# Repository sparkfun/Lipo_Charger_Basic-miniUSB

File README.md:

SparkFun Lipo Charger Basic - miniUSB
=======================================

[*SparkFun Lipo Charger Basic - miniUSB (PRT-10401)*](https://www.sparkfun.com/products/10401)

If you need to charge LiPo batteries, this simple charger will do just that. It is designed to charge single-cell Li-Ion or Li-Polymer batteries.
The board incorporates a charging circuit, status LED, connector for your battery (JST-type used in the batteries we carry), and a mini-USB connector.

Repository Contents
-------------------
* **/Hardware** - All Eagle design files (.brd, .sch)

License Information
-------------------
The hardware is released under [Creative Commons ShareAlike 4.0 International](https://creativecommons.org/licenses/by-sa/4.0/).

Distributed as-is; no warranty is given.

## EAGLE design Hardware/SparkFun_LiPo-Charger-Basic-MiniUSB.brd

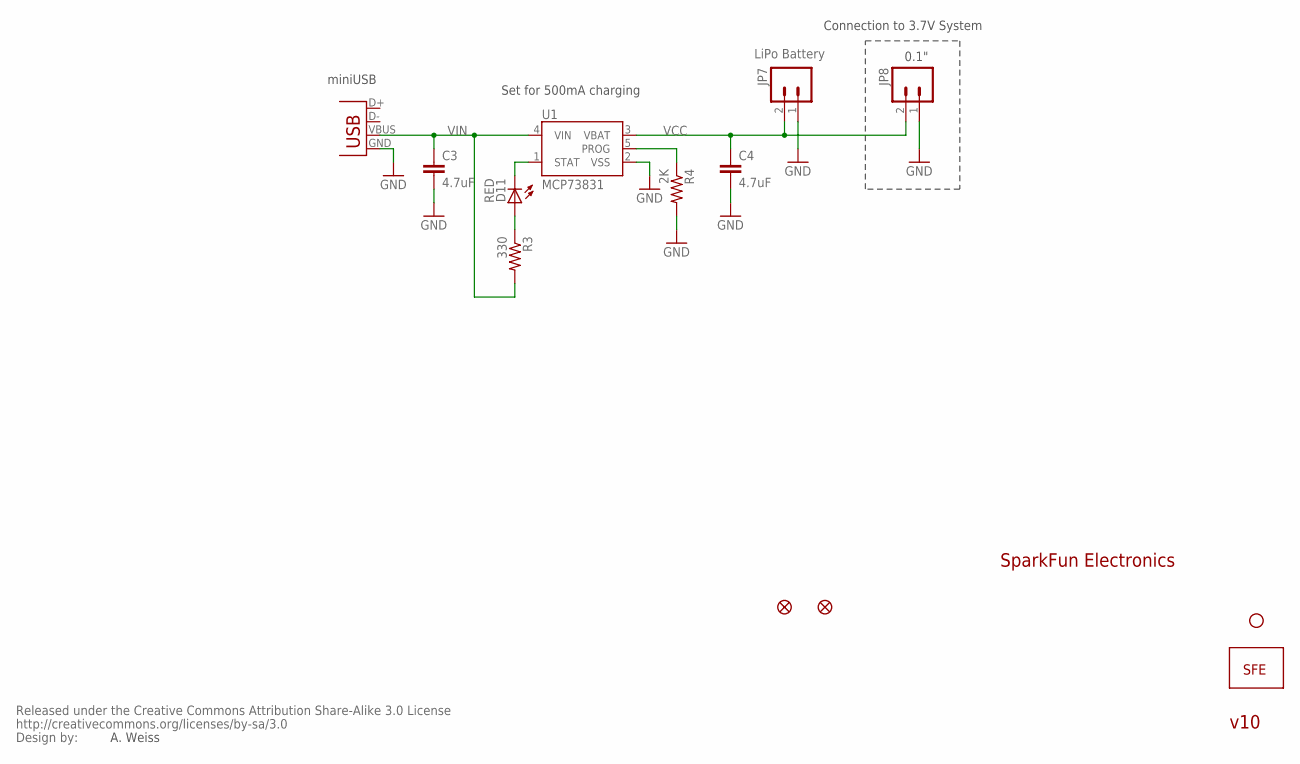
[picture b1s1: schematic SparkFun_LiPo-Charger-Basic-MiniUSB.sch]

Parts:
C3, C4: 4.7uF; 0402-CAP
D11: RED; LED-0603
JP1: LOGO-SFESK; SFE-LOGO-FLAME
JP2: STAND-OFF
JP3, JP4: FIDUCIAL1X2; FIDUCIAL-1X2
JP7: LiPo Battery; JST-2-SMD
JP8: M02PTH; 1X02
R3: 330; 0402-RES
R4: 2K; 0402-RES
U1: MCP73831; SOT23-5
U$1: CREATIVE_COMMONS
X1: Micro USB; USB-MINIB

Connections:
GND: C3.2, C4.2, JP7.1, JP8.1, R4.2, U1.2 (VSS), X1.GND
unnamed: D11.A, R3.1
PROG: R4.1, U1.5 (PROG)
STAT: D11.C, U1.1 (STAT)
VCC: C4.1, JP7.2, JP8.2, U1.3 (VBAT)
VIN: C3.1, R3.2, U1.4 (VIN), X1.VBUS

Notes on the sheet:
Set for 500mA charging
Connection to 3.7V System
0.1"
A. Weiss
miniUSB
v10
SparkFun Electronics

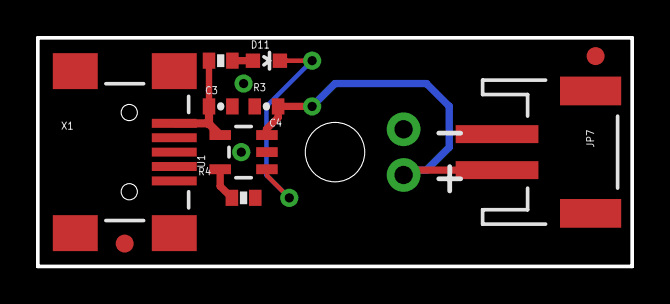
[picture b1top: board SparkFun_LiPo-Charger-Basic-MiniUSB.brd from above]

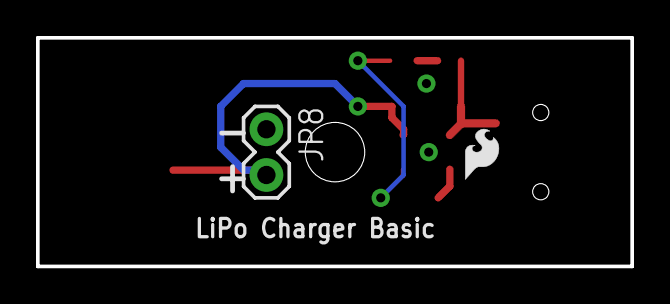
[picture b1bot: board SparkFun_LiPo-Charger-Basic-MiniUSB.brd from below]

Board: 2 copper layers, 33.0 x 12.7 mm, 14 parts (2 on the bottom side), 6 nets.

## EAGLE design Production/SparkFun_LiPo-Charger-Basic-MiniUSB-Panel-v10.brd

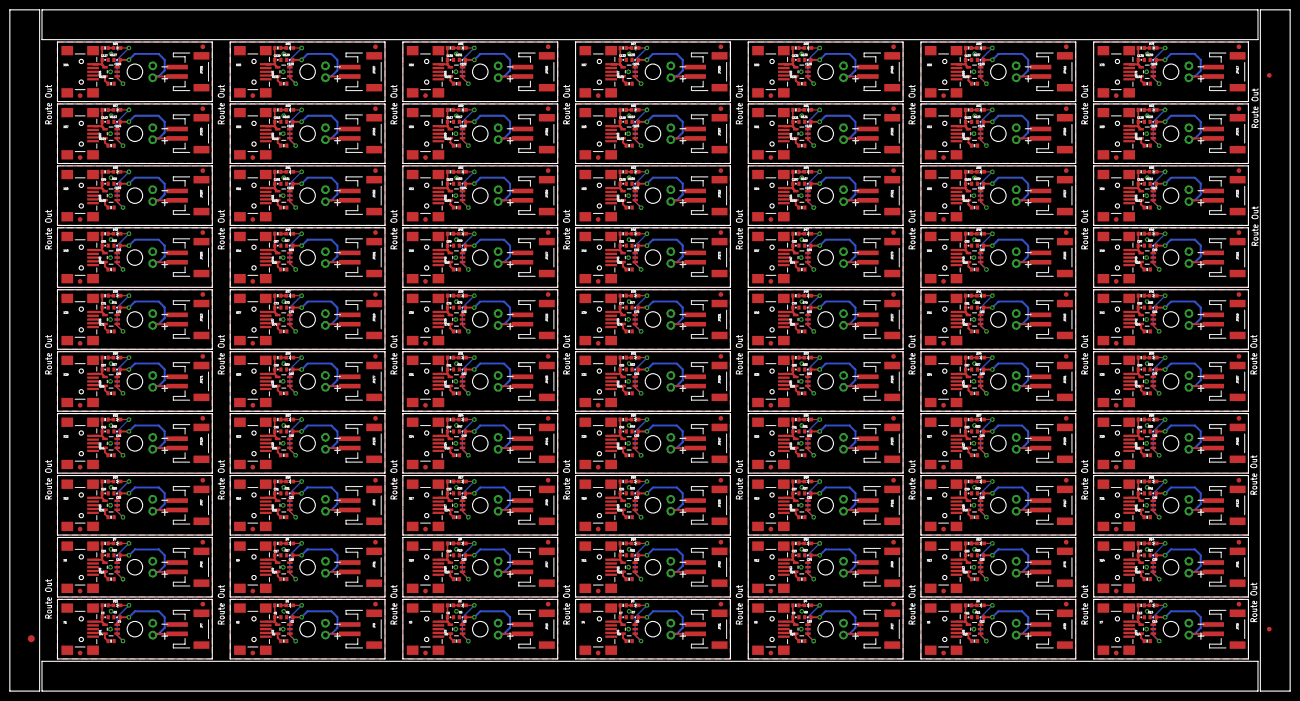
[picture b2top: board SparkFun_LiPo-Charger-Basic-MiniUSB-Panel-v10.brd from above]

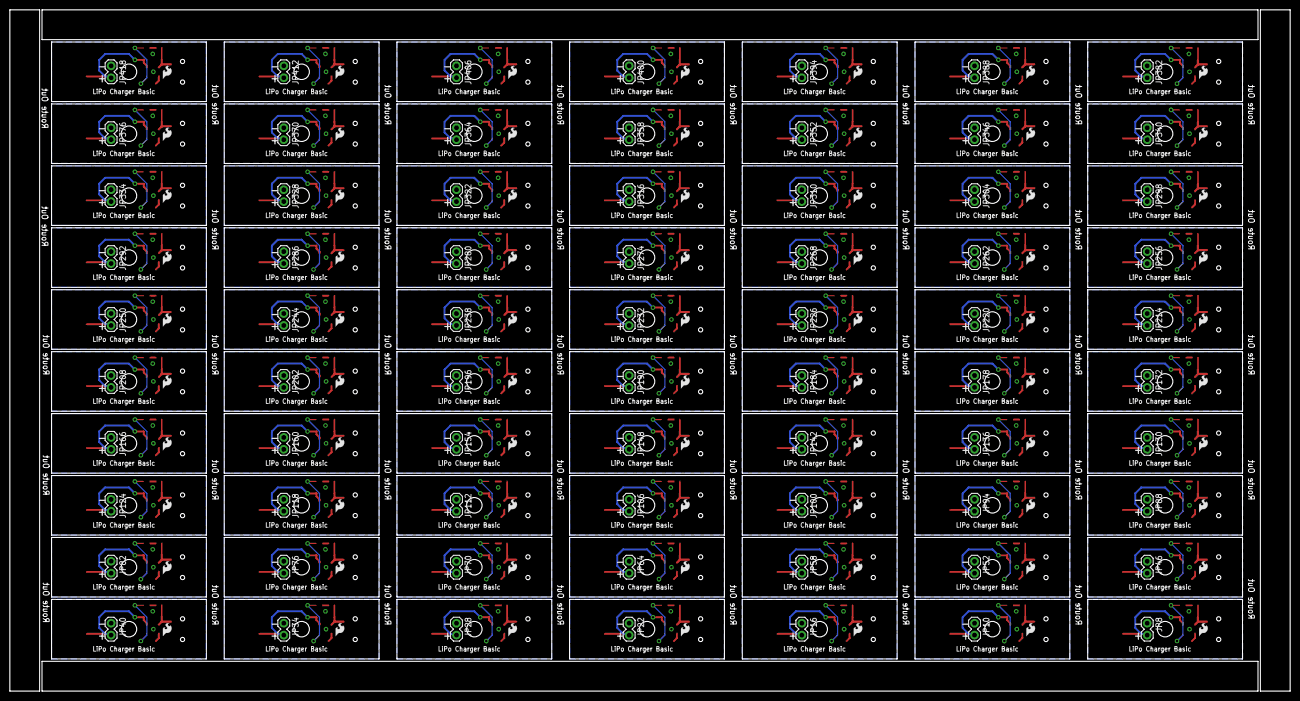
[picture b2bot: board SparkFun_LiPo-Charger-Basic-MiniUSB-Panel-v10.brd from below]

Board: 2 copper layers, 273.1 x 145.3 mm, 913 parts (140 on the bottom side), 420 nets.

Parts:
C1, C2, C3, C4, C5, C6, C7, C8, C9, C10, C11, C12, C13, C14, C15, C16, C17, C18, C19, C20, C21, C22, C23, C24, C25, C26, C27, C28, C29, C30, C31, C32, C33, C34, C35, C36, C37, C38, C39, C40, C41, C42, C43, C44, C45, C46, C47, C48, C49, C50, C51, C52, C53, C54, C55, C56, C57, C58, C59, C60, C61, C62, C63, C64, C65, C66, C67, C68, C69, C70, C71, C72, C73, C74, C75, C76, C77, C78, C79, C80, C81, C82, C83, C84, C85, C86, C87, C88, C89, C90, C91, C92, C93, C94, C95, C96, C97, C98, C99, C100, C101, C102, C103, C104, C105, C106, C107, C108, C109, C110, C111, C112, C113, C114, C115, C116, C117, C118, C119, C120, C121, C122, C123, C124, C125, C126, C127, C128, C129, C130, C131, C132, C133, C134, C135, C136, C137, C138, C139, C140: 4.7uF; 0402-CAP
D1, D2, D3, D4, D5, D6, D7, D8, D9, D10, D11, D12, D13, D14, D15, D16, D17, D18, D19, D20, D21, D22, D23, D24, D25, D26, D27, D28, D29, D30, D31, D32, D33, D34, D35, D36, D37, D38, D39, D40, D41, D42, D43, D44, D45, D46, D47, D48, D49, D50, D51, D52, D53, D54, D55, D56, D57, D58, D59, D60, D61, D62, D63, D64, D65, D66, D67, D68, D69, D70: RED; LED-0603
E$1: FIDUCIAL-1.5X3
E$4, E$5: FIDUCIAL-1X2
JP1, JP5, JP13, JP19, JP25, JP31, JP37, JP43, JP49, JP55, JP61, JP67, JP73, JP79, JP85, JP91, JP97, JP103, JP109, JP115, JP121, JP127, JP133, JP139, JP145, JP151, JP157, JP163, JP169, JP175, JP181, JP187, JP193, JP199, JP205, JP211, JP217, JP223, JP229, JP235, JP241, JP247, JP253, JP259, JP265, JP271, JP277, JP283, JP289, JP295, JP301, JP307, JP313, JP319, JP325, JP331, JP337, JP343, JP349, JP355, JP361, JP367, JP373, JP379, JP385, JP391, JP397, JP403, JP409, JP415: LOGO-SFESK; SFE-LOGO-FLAME
JP2, JP6, JP14, JP20, JP26, JP32, JP38, JP44, JP50, JP56, JP62, JP68, JP74, JP80, JP86, JP92, JP98, JP104, JP110, JP116, JP122, JP128, JP134, JP140, JP146, JP152, JP158, JP164, JP170, JP176, JP182, JP188, JP194, JP200, JP206, JP212, JP218, JP224, JP230, JP236, JP242, JP248, JP254, JP260, JP266, JP272, JP278, JP284, JP290, JP296, JP302, JP308, JP314, JP320, JP326, JP332, JP338, JP344, JP350, JP356, JP362, JP368, JP374, JP380, JP386, JP392, JP398, JP404, JP410, JP416: STAND-OFF
JP3, JP4, JP11, JP12, JP17, JP18, JP23, JP24, JP29, JP30, JP35, JP36, JP41, JP42, JP47, JP48, JP53, JP54, JP59, JP60, JP65, JP66, JP71, JP72, JP77, JP78, JP83, JP84, JP89, JP90, JP95, JP96, JP101, JP102, JP107, JP108, JP113, JP114, JP119, JP120, JP125, JP126, JP131, JP132, JP137, JP138, JP143, JP144, JP149, JP150, JP155, JP156, JP161, JP162, JP167, JP168, JP173, JP174, JP179, JP180, JP185, JP186, JP191, JP192, JP197, JP198, JP203, JP204, JP209, JP210, JP215, JP216, JP221, JP222, JP227, JP228, JP233, JP234, JP239, JP240, JP245, JP246, JP251, JP252, JP257, JP258, JP263, JP264, JP269, JP270, JP275, JP276, JP281, JP282, JP287, JP288, JP293, JP294, JP299, JP300, JP305, JP306, JP311, JP312, JP317, JP318, JP323, JP324, JP329, JP330, JP335, JP336, JP341, JP342, JP347, JP348, JP353, JP354, JP359, JP360, JP365, JP366, JP371, JP372, JP377, JP378, JP383, JP384, JP389, JP390, JP395, JP396, JP401, JP402, JP407, JP408, JP413, JP414, JP419, JP420: FIDUCIAL1X2; FIDUCIAL-1X2
JP7, JP9, JP15, JP21, JP27, JP33, JP39, JP45, JP51, JP57, JP63, JP69, JP75, JP81, JP87, JP93, JP99, JP105, JP111, JP117, JP123, JP129, JP135, JP141, JP147, JP153, JP159, JP165, JP171, JP177, JP183, JP189, JP195, JP201, JP207, JP213, JP219, JP225, JP231, JP237, JP243, JP249, JP255, JP261, JP267, JP273, JP279, JP285, JP291, JP297, JP303, JP309, JP315, JP321, JP327, JP333, JP339, JP345, JP351, JP357, JP363, JP369, JP375, JP381, JP387, JP393, JP399, JP405, JP411, JP417: LiPo Battery; JST-2-SMD
JP8, JP10, JP16, JP22, JP28, JP34, JP40, JP46, JP52, JP58, JP64, JP70, JP76, JP82, JP88, JP94, JP100, JP106, JP112, JP118, JP124, JP130, JP136, JP142, JP148, JP154, JP160, JP166, JP172, JP178, JP184, JP190, JP196, JP202, JP208, JP214, JP220, JP226, JP232, JP238, JP244, JP250, JP256, JP262, JP268, JP274, JP280, JP286, JP292, JP298, JP304, JP310, JP316, JP322, JP328, JP334, JP340, JP346, JP352, JP358, JP364, JP370, JP376, JP382, JP388, JP394, JP400, JP406, JP412, JP418: 1X02
R1, R3, R5, R7, R9, R11, R13, R15, R17, R19, R21, R23, R25, R27, R29, R31, R33, R35, R37, R39, R41, R43, R45, R47, R49, R51, R53, R55, R57, R59, R61, R63, R65, R67, R69, R71, R73, R75, R77, R79, R81, R83, R85, R87, R89, R91, R93, R95, R97, R99, R101, R103, R105, R107, R109, R111, R113, R115, R117, R119, R121, R123, R125, R127, R129, R131, R133, R135, R137, R139: 330; 0402-RES
R2, R4, R6, R8, R10, R12, R14, R16, R18, R20, R22, R24, R26, R28, R30, R32, R34, R36, R38, R40, R42, R44, R46, R48, R50, R52, R54, R56, R58, R60, R62, R64, R66, R68, R70, R72, R74, R76, R78, R80, R82, R84, R86, R88, R90, R92, R94, R96, R98, R100, R102, R104, R106, R108, R110, R112, R114, R116, R118, R120, R122, R124, R126, R128, R130, R132, R134, R136, R138, R140: 2K; 0402-RES
U1, U2, U3, U4, U5, U6, U7, U8, U9, U10, U11, U12, U13, U14, U15, U16, U17, U18, U19, U20, U21, U22, U23, U24, U25, U26, U27, U28, U29, U30, U31, U32, U33, U34, U35, U36, U37, U38, U39, U40, U41, U42, U43, U44, U45, U46, U47, U48, U49, U50, U51, U52, U53, U54, U55, U56, U57, U58, U59, U60, U61, U62, U63, U64, U65, U66, U67, U68, U69, U70: MCP73831; SOT23-5
X1, X2, X3, X4, X5, X6, X7, X8, X9, X10, X11, X12, X13, X14, X15, X16, X17, X18, X19, X20, X21, X22, X23, X24, X25, X26, X27, X28, X29, X30, X31, X32, X33, X34, X35, X36, X37, X38, X39, X40, X41, X42, X43, X44, X45, X46, X47, X48, X49, X50, X51, X52, X53, X54, X55, X56, X57, X58, X59, X60, X61, X62, X63, X64, X65, X66, X67, X68, X69, X70: Micro USB; USB-MINIB

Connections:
GND: C3.2, C4.2, JP7.1, JP8.1, R4.2, U1.2, X1.GND
GND1: C1.2, C2.2, JP9.1, JP10.1, R2.2, U2.2, X2.GND
GND2: C5.2, C6.2, JP15.1, JP16.1, R6.2, U3.2, X3.GND
GND3: C7.2, C8.2, JP21.1, JP22.1, R8.2, U4.2, X4.GND
GND4: C9.2, C10.2, JP27.1, JP28.1, R10.2, U5.2, X5.GND
GND5: C11.2, C12.2, JP33.1, JP34.1, R12.2, U6.2, X6.GND
GND6: C13.2, C14.2, JP39.1, JP40.1, R14.2, U7.2, X7.GND
GND7: C15.2, C16.2, JP45.1, JP46.1, R16.2, U8.2, X8.GND
GND8: C17.2, C18.2, JP51.1, JP52.1, R18.2, U9.2, X9.GND
GND9: C19.2, C20.2, JP57.1, JP58.1, R20.2, U10.2, X10.GND
GND10: C21.2, C22.2, JP63.1, JP64.1, R22.2, U11.2, X11.GND
GND11: C23.2, C24.2, JP69.1, JP70.1, R24.2, U12.2, X12.GND
GND12: C25.2, C26.2, JP75.1, JP76.1, R26.2, U13.2, X13.GND
GND13: C27.2, C28.2, JP81.1, JP82.1, R28.2, U14.2, X14.GND
GND14: C29.2, C30.2, JP87.1, JP88.1, R30.2, U15.2, X15.GND
GND15: C31.2, C32.2, JP93.1, JP94.1, R32.2, U16.2, X16.GND
GND16: C33.2, C34.2, JP99.1, JP100.1, R34.2, U17.2, X17.GND
GND17: C35.2, C36.2, JP105.1, JP106.1, R36.2, U18.2, X18.GND
GND18: C37.2, C38.2, JP111.1, JP112.1, R38.2, U19.2, X19.GND
GND19: C39.2, C40.2, JP117.1, JP118.1, R40.2, U20.2, X20.GND
GND20: C41.2, C42.2, JP123.1, JP124.1, R42.2, U21.2, X21.GND
GND21: C43.2, C44.2, JP129.1, JP130.1, R44.2, U22.2, X22.GND
GND22: C45.2, C46.2, JP135.1, JP136.1, R46.2, U23.2, X23.GND
GND23: C47.2, C48.2, JP141.1, JP142.1, R48.2, U24.2, X24.GND
GND24: C49.2, C50.2, JP147.1, JP148.1, R50.2, U25.2, X25.GND
GND25: C51.2, C52.2, JP153.1, JP154.1, R52.2, U26.2, X26.GND
GND26: C53.2, C54.2, JP159.1, JP160.1, R54.2, U27.2, X27.GND
GND27: C55.2, C56.2, JP165.1, JP166.1, R56.2, U28.2, X28.GND
GND28: C57.2, C58.2, JP171.1, JP172.1, R58.2, U29.2, X29.GND
GND29: C59.2, C60.2, JP177.1, JP178.1, R60.2, U30.2, X30.GND
GND30: C61.2, C62.2, JP183.1, JP184.1, R62.2, U31.2, X31.GND
GND31: C63.2, C64.2, JP189.1, JP190.1, R64.2, U32.2, X32.GND
GND32: C65.2, C66.2, JP195.1, JP196.1, R66.2, U33.2, X33.GND
GND33: C67.2, C68.2, JP201.1, JP202.1, R68.2, U34.2, X34.GND
GND34: C69.2, C70.2, JP207.1, JP208.1, R70.2, U35.2, X35.GND
GND35: C71.2, C72.2, JP213.1, JP214.1, R72.2, U36.2, X36.GND
GND36: C73.2, C74.2, JP219.1, JP220.1, R74.2, U37.2, X37.GND
GND37: C75.2, C76.2, JP225.1, JP226.1, R76.2, U38.2, X38.GND
GND38: C77.2, C78.2, JP231.1, JP232.1, R78.2, U39.2, X39.GND
GND39: C79.2, C80.2, JP237.1, JP238.1, R80.2, U40.2, X40.GND
GND40: C81.2, C82.2, JP243.1, JP244.1, R82.2, U41.2, X41.GND
GND41: C83.2, C84.2, JP249.1, JP250.1, R84.2, U42.2, X42.GND
GND42: C85.2, C86.2, JP255.1, JP256.1, R86.2, U43.2, X43.GND
GND43: C87.2, C88.2, JP261.1, JP262.1, R88.2, U44.2, X44.GND
GND44: C89.2, C90.2, JP267.1, JP268.1, R90.2, U45.2, X45.GND
GND45: C91.2, C92.2, JP273.1, JP274.1, R92.2, U46.2, X46.GND
GND46: C93.2, C94.2, JP279.1, JP280.1, R94.2, U47.2, X47.GND
GND47: C95.2, C96.2, JP285.1, JP286.1, R96.2, U48.2, X48.GND
GND48: C97.2, C98.2, JP291.1, JP292.1, R98.2, U49.2, X49.GND
GND49: C99.2, C100.2, JP297.1, JP298.1, R100.2, U50.2, X50.GND
GND50: C101.2, C102.2, JP303.1, JP304.1, R102.2, U51.2, X51.GND
GND51: C103.2, C104.2, JP309.1, JP310.1, R104.2, U52.2, X52.GND
GND52: C105.2, C106.2, JP315.1, JP316.1, R106.2, U53.2, X53.GND
GND53: C107.2, C108.2, JP321.1, JP322.1, R108.2, U54.2, X54.GND
GND54: C109.2, C110.2, JP327.1, JP328.1, R110.2, U55.2, X55.GND
GND55: C111.2, C112.2, JP333.1, JP334.1, R112.2, U56.2, X56.GND
GND56: C113.2, C114.2, JP339.1, JP340.1, R114.2, U57.2, X57.GND
GND57: C115.2, C116.2, JP345.1, JP346.1, R116.2, U58.2, X58.GND
GND58: C117.2, C118.2, JP351.1, JP352.1, R118.2, U59.2, X59.GND
GND59: C119.2, C120.2, JP357.1, JP358.1, R120.2, U60.2, X60.GND
GND60: C121.2, C122.2, JP363.1, JP364.1, R122.2, U61.2, X61.GND
GND61: C123.2, C124.2, JP369.1, JP370.1, R124.2, U62.2, X62.GND
GND62: C125.2, C126.2, JP375.1, JP376.1, R126.2, U63.2, X63.GND
GND63: C127.2, C128.2, JP381.1, JP382.1, R128.2, U64.2, X64.GND
GND64: C129.2, C130.2, JP387.1, JP388.1, R130.2, U65.2, X65.GND
GND65: C131.2, C132.2, JP393.1, JP394.1, R132.2, U66.2, X66.GND
GND66: C133.2, C134.2, JP399.1, JP400.1, R134.2, U67.2, X67.GND
GND67: C135.2, C136.2, JP405.1, JP406.1, R136.2, U68.2, X68.GND
GND68: C137.2, C138.2, JP411.1, JP412.1, R138.2, U69.2, X69.GND
GND69: C139.2, C140.2, JP417.1, JP418.1, R140.2, U70.2, X70.GND
unnamed: D1.A, R1.1
unnamed: D2.A, R5.1
unnamed: D11.A, R3.1
unnamed: D3.A, R7.1
unnamed: D4.A, R9.1
unnamed: D5.A, R11.1
unnamed: D6.A, R13.1
unnamed: D7.A, R15.1
unnamed: D8.A, R17.1
unnamed: D9.A, R19.1
unnamed: D10.A, R21.1
unnamed: D12.A, R23.1
unnamed: D13.A, R25.1
unnamed: D14.A, R27.1
unnamed: D15.A, R29.1
unnamed: D16.A, R31.1
unnamed: D17.A, R33.1
unnamed: D18.A, R35.1
unnamed: D19.A, R37.1
unnamed: D20.A, R39.1
unnamed: D21.A, R41.1
unnamed: D22.A, R43.1
unnamed: D23.A, R45.1
unnamed: D24.A, R47.1
unnamed: D25.A, R49.1
unnamed: D26.A, R51.1
unnamed: D27.A, R53.1
unnamed: D28.A, R55.1
unnamed: D29.A, R57.1
unnamed: D30.A, R59.1
unnamed: D31.A, R61.1
unnamed: D32.A, R63.1
unnamed: D33.A, R65.1
unnamed: D34.A, R67.1
unnamed: D35.A, R69.1
unnamed: D36.A, R71.1
unnamed: D37.A, R73.1
unnamed: D38.A, R75.1
unnamed: D39.A, R77.1
unnamed: D40.A, R79.1
unnamed: D41.A, R81.1
unnamed: D42.A, R83.1
unnamed: D43.A, R85.1
unnamed: D44.A, R87.1
unnamed: D45.A, R89.1
unnamed: D46.A, R91.1
unnamed: D47.A, R93.1
unnamed: D48.A, R95.1
unnamed: D49.A, R97.1
unnamed: D50.A, R99.1
unnamed: D51.A, R101.1
unnamed: D52.A, R103.1
unnamed: D53.A, R105.1
unnamed: D54.A, R107.1
unnamed: D55.A, R109.1
unnamed: D56.A, R111.1
unnamed: D57.A, R113.1
unnamed: D58.A, R115.1
unnamed: D59.A, R117.1
unnamed: D60.A, R119.1
unnamed: D61.A, R121.1
unnamed: D62.A, R123.1
unnamed: D63.A, R125.1
unnamed: D64.A, R127.1
unnamed: D65.A, R129.1
unnamed: D66.A, R131.1
unnamed: D67.A, R133.1
unnamed: D68.A, R135.1
unnamed: D69.A, R137.1
unnamed: D70.A, R139.1
PROG: R4.1, U1.5
PROG1: R2.1, U2.5
PROG2: R6.1, U3.5
PROG3: R8.1, U4.5
PROG4: R10.1, U5.5
PROG5: R12.1, U6.5
PROG6: R14.1, U7.5
PROG7: R16.1, U8.5
PROG8: R18.1, U9.5
PROG9: R20.1, U10.5
PROG10: R22.1, U11.5
PROG11: R24.1, U12.5
PROG12: R26.1, U13.5
PROG13: R28.1, U14.5
PROG14: R30.1, U15.5
PROG15: R32.1, U16.5
PROG16: R34.1, U17.5
PROG17: R36.1, U18.5
PROG18: R38.1, U19.5
PROG19: R40.1, U20.5
PROG20: R42.1, U21.5
PROG21: R44.1, U22.5
PROG22: R46.1, U23.5
PROG23: R48.1, U24.5
PROG24: R50.1, U25.5
PROG25: R52.1, U26.5
PROG26: R54.1, U27.5
PROG27: R56.1, U28.5
PROG28: R58.1, U29.5
PROG29: R60.1, U30.5
PROG30: R62.1, U31.5
PROG31: R64.1, U32.5
PROG32: R66.1, U33.5
PROG33: R68.1, U34.5
PROG34: R70.1, U35.5
PROG35: R72.1, U36.5
PROG36: R74.1, U37.5
PROG37: R76.1, U38.5
PROG38: R78.1, U39.5
PROG39: R80.1, U40.5
PROG40: R82.1, U41.5
PROG41: R84.1, U42.5
PROG42: R86.1, U43.5
PROG43: R88.1, U44.5
PROG44: R90.1, U45.5
PROG45: R92.1, U46.5
PROG46: R94.1, U47.5
PROG47: R96.1, U48.5
PROG48: R98.1, U49.5
PROG49: R100.1, U50.5
PROG50: R102.1, U51.5
PROG51: R104.1, U52.5
PROG52: R106.1, U53.5
PROG53: R108.1, U54.5
PROG54: R110.1, U55.5
PROG55: R112.1, U56.5
PROG56: R114.1, U57.5
PROG57: R116.1, U58.5
PROG58: R118.1, U59.5
PROG59: R120.1, U60.5
PROG60: R122.1, U61.5
PROG61: R124.1, U62.5
PROG62: R126.1, U63.5
PROG63: R128.1, U64.5
PROG64: R130.1, U65.5
PROG65: R132.1, U66.5
PROG66: R134.1, U67.5
PROG67: R136.1, U68.5
PROG68: R138.1, U69.5
PROG69: R140.1, U70.5
STAT: D11.C, U1.1
STAT1: D1.C, U2.1
STAT2: D2.C, U3.1
STAT3: D3.C, U4.1
STAT4: D4.C, U5.1
STAT5: D5.C, U6.1
STAT6: D6.C, U7.1
STAT7: D7.C, U8.1
STAT8: D8.C, U9.1
STAT9: D9.C, U10.1
STAT10: D10.C, U11.1
STAT11: D12.C, U12.1
STAT12: D13.C, U13.1
STAT13: D14.C, U14.1
STAT14: D15.C, U15.1
STAT15: D16.C, U16.1
STAT16: D17.C, U17.1
STAT17: D18.C, U18.1
STAT18: D19.C, U19.1
STAT19: D20.C, U20.1
STAT20: D21.C, U21.1
STAT21: D22.C, U22.1
STAT22: D23.C, U23.1
STAT23: D24.C, U24.1
STAT24: D25.C, U25.1
STAT25: D26.C, U26.1
STAT26: D27.C, U27.1
STAT27: D28.C, U28.1
STAT28: D29.C, U29.1
STAT29: D30.C, U30.1
STAT30: D31.C, U31.1
STAT31: D32.C, U32.1
STAT32: D33.C, U33.1
STAT33: D34.C, U34.1
STAT34: D35.C, U35.1
STAT35: D36.C, U36.1
STAT36: D37.C, U37.1
STAT37: D38.C, U38.1
STAT38: D39.C, U39.1
STAT39: D40.C, U40.1
STAT40: D41.C, U41.1
STAT41: D42.C, U42.1
STAT42: D43.C, U43.1
STAT43: D44.C, U44.1
STAT44: D45.C, U45.1
STAT45: D46.C, U46.1
STAT46: D47.C, U47.1
STAT47: D48.C, U48.1
STAT48: D49.C, U49.1
STAT49: D50.C, U50.1
STAT50: D51.C, U51.1
STAT51: D52.C, U52.1
STAT52: D53.C, U53.1
STAT53: D54.C, U54.1
STAT54: D55.C, U55.1
STAT55: D56.C, U56.1
STAT56: D57.C, U57.1
STAT57: D58.C, U58.1
STAT58: D59.C, U59.1
STAT59: D60.C, U60.1
STAT60: D61.C, U61.1
STAT61: D62.C, U62.1
STAT62: D63.C, U63.1
STAT63: D64.C, U64.1
STAT64: D65.C, U65.1
STAT65: D66.C, U66.1
STAT66: D67.C, U67.1
STAT67: D68.C, U68.1
STAT68: D69.C, U69.1
STAT69: D70.C, U70.1
VCC: C4.1, JP7.2, JP8.2, U1.3
VCC1: C2.1, JP9.2, JP10.2, U2.3
VCC2: C6.1, JP15.2, JP16.2, U3.3
VCC3: C8.1, JP21.2, JP22.2, U4.3
VCC4: C10.1, JP27.2, JP28.2, U5.3
VCC5: C12.1, JP33.2, JP34.2, U6.3
VCC6: C14.1, JP39.2, JP40.2, U7.3
VCC7: C16.1, JP45.2, JP46.2, U8.3
VCC8: C18.1, JP51.2, JP52.2, U9.3
VCC9: C20.1, JP57.2, JP58.2, U10.3
VCC10: C22.1, JP63.2, JP64.2, U11.3
VCC11: C24.1, JP69.2, JP70.2, U12.3
VCC12: C26.1, JP75.2, JP76.2, U13.3
VCC13: C28.1, JP81.2, JP82.2, U14.3
VCC14: C30.1, JP87.2, JP88.2, U15.3
VCC15: C32.1, JP93.2, JP94.2, U16.3
VCC16: C34.1, JP99.2, JP100.2, U17.3
VCC17: C36.1, JP105.2, JP106.2, U18.3
VCC18: C38.1, JP111.2, JP112.2, U19.3
VCC19: C40.1, JP117.2, JP118.2, U20.3
VCC20: C42.1, JP123.2, JP124.2, U21.3
VCC21: C44.1, JP129.2, JP130.2, U22.3
VCC22: C46.1, JP135.2, JP136.2, U23.3
VCC23: C48.1, JP141.2, JP142.2, U24.3
VCC24: C50.1, JP147.2, JP148.2, U25.3
VCC25: C52.1, JP153.2, JP154.2, U26.3
VCC26: C54.1, JP159.2, JP160.2, U27.3
VCC27: C56.1, JP165.2, JP166.2, U28.3
VCC28: C58.1, JP171.2, JP172.2, U29.3
VCC29: C60.1, JP177.2, JP178.2, U30.3
VCC30: C62.1, JP183.2, JP184.2, U31.3
VCC31: C64.1, JP189.2, JP190.2, U32.3
VCC32: C66.1, JP195.2, JP196.2, U33.3
VCC33: C68.1, JP201.2, JP202.2, U34.3
VCC34: C70.1, JP207.2, JP208.2, U35.3
VCC35: C72.1, JP213.2, JP214.2, U36.3
VCC36: C74.1, JP219.2, JP220.2, U37.3
VCC37: C76.1, JP225.2, JP226.2, U38.3
VCC38: C78.1, JP231.2, JP232.2, U39.3
VCC39: C80.1, JP237.2, JP238.2, U40.3
VCC40: C82.1, JP243.2, JP244.2, U41.3
VCC41: C84.1, JP249.2, JP250.2, U42.3
VCC42: C86.1, JP255.2, JP256.2, U43.3
VCC43: C88.1, JP261.2, JP262.2, U44.3
VCC44: C90.1, JP267.2, JP268.2, U45.3
VCC45: C92.1, JP273.2, JP274.2, U46.3
VCC46: C94.1, JP279.2, JP280.2, U47.3
VCC47: C96.1, JP285.2, JP286.2, U48.3
VCC48: C98.1, JP291.2, JP292.2, U49.3
VCC49: C100.1, JP297.2, JP298.2, U50.3
VCC50: C102.1, JP303.2, JP304.2, U51.3
VCC51: C104.1, JP309.2, JP310.2, U52.3
VCC52: C106.1, JP315.2, JP316.2, U53.3
VCC53: C108.1, JP321.2, JP322.2, U54.3
VCC54: C110.1, JP327.2, JP328.2, U55.3
VCC55: C112.1, JP333.2, JP334.2, U56.3
VCC56: C114.1, JP339.2, JP340.2, U57.3
VCC57: C116.1, JP345.2, JP346.2, U58.3
VCC58: C118.1, JP351.2, JP352.2, U59.3
VCC59: C120.1, JP357.2, JP358.2, U60.3
VCC60: C122.1, JP363.2, JP364.2, U61.3
VCC61: C124.1, JP369.2, JP370.2, U62.3
VCC62: C126.1, JP375.2, JP376.2, U63.3
VCC63: C128.1, JP381.2, JP382.2, U64.3
VCC64: C130.1, JP387.2, JP388.2, U65.3
VCC65: C132.1, JP393.2, JP394.2, U66.3
VCC66: C134.1, JP399.2, JP400.2, U67.3
VCC67: C136.1, JP405.2, JP406.2, U68.3
VCC68: C138.1, JP411.2, JP412.2, U69.3
VCC69: C140.1, JP417.2, JP418.2, U70.3
VIN: C3.1, R3.2, U1.4, X1.VBUS
VIN1: C1.1, R1.2, U2.4, X2.VBUS
VIN2: C5.1, R5.2, U3.4, X3.VBUS
VIN3: C7.1, R7.2, U4.4, X4.VBUS
VIN4: C9.1, R9.2, U5.4, X5.VBUS
VIN5: C11.1, R11.2, U6.4, X6.VBUS
VIN6: C13.1, R13.2, U7.4, X7.VBUS
VIN7: C15.1, R15.2, U8.4, X8.VBUS
VIN8: C17.1, R17.2, U9.4, X9.VBUS
VIN9: C19.1, R19.2, U10.4, X10.VBUS
VIN10: C21.1, R21.2, U11.4, X11.VBUS
VIN11: C23.1, R23.2, U12.4, X12.VBUS
VIN12: C25.1, R25.2, U13.4, X13.VBUS
VIN13: C27.1, R27.2, U14.4, X14.VBUS
VIN14: C29.1, R29.2, U15.4, X15.VBUS
VIN15: C31.1, R31.2, U16.4, X16.VBUS
VIN16: C33.1, R33.2, U17.4, X17.VBUS
VIN17: C35.1, R35.2, U18.4, X18.VBUS
VIN18: C37.1, R37.2, U19.4, X19.VBUS
VIN19: C39.1, R39.2, U20.4, X20.VBUS
VIN20: C41.1, R41.2, U21.4, X21.VBUS
VIN21: C43.1, R43.2, U22.4, X22.VBUS
VIN22: C45.1, R45.2, U23.4, X23.VBUS
VIN23: C47.1, R47.2, U24.4, X24.VBUS
VIN24: C49.1, R49.2, U25.4, X25.VBUS
VIN25: C51.1, R51.2, U26.4, X26.VBUS
VIN26: C53.1, R53.2, U27.4, X27.VBUS
VIN27: C55.1, R55.2, U28.4, X28.VBUS
VIN28: C57.1, R57.2, U29.4, X29.VBUS
VIN29: C59.1, R59.2, U30.4, X30.VBUS
VIN30: C61.1, R61.2, U31.4, X31.VBUS
VIN31: C63.1, R63.2, U32.4, X32.VBUS
VIN32: C65.1, R65.2, U33.4, X33.VBUS
VIN33: C67.1, R67.2, U34.4, X34.VBUS
VIN34: C69.1, R69.2, U35.4, X35.VBUS
VIN35: C71.1, R71.2, U36.4, X36.VBUS
VIN36: C73.1, R73.2, U37.4, X37.VBUS
VIN37: C75.1, R75.2, U38.4, X38.VBUS
VIN38: C77.1, R77.2, U39.4, X39.VBUS
VIN39: C79.1, R79.2, U40.4, X40.VBUS
VIN40: C81.1, R81.2, U41.4, X41.VBUS
VIN41: C83.1, R83.2, U42.4, X42.VBUS
VIN42: C85.1, R85.2, U43.4, X43.VBUS
VIN43: C87.1, R87.2, U44.4, X44.VBUS
VIN44: C89.1, R89.2, U45.4, X45.VBUS
VIN45: C91.1, R91.2, U46.4, X46.VBUS
VIN46: C93.1, R93.2, U47.4, X47.VBUS
VIN47: C95.1, R95.2, U48.4, X48.VBUS
VIN48: C97.1, R97.2, U49.4, X49.VBUS
VIN49: C99.1, R99.2, U50.4, X50.VBUS
VIN50: C101.1, R101.2, U51.4, X51.VBUS
VIN51: C103.1, R103.2, U52.4, X52.VBUS
VIN52: C105.1, R105.2, U53.4, X53.VBUS
VIN53: C107.1, R107.2, U54.4, X54.VBUS
VIN54: C109.1, R109.2, U55.4, X55.VBUS
VIN55: C111.1, R111.2, U56.4, X56.VBUS
VIN56: C113.1, R113.2, U57.4, X57.VBUS
VIN57: C115.1, R115.2, U58.4, X58.VBUS
VIN58: C117.1, R117.2, U59.4, X59.VBUS
VIN59: C119.1, R119.2, U60.4, X60.VBUS
VIN60: C121.1, R121.2, U61.4, X61.VBUS
VIN61: C123.1, R123.2, U62.4, X62.VBUS
VIN62: C125.1, R125.2, U63.4, X63.VBUS
VIN63: C127.1, R127.2, U64.4, X64.VBUS
VIN64: C129.1, R129.2, U65.4, X65.VBUS
VIN65: C131.1, R131.2, U66.4, X66.VBUS
VIN66: C133.1, R133.2, U67.4, X67.VBUS
VIN67: C135.1, R135.2, U68.4, X68.VBUS
VIN68: C137.1, R137.2, U69.4, X69.VBUS
VIN69: C139.1, R139.2, U70.4, X70.VBUS

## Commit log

2015-02-23 Adding hardware files
2015-02-23 Adding image to readme
2015-08-10 created panel v10

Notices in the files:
parts and their libraries:
SparkFun: Released under the Creative Commons Attribution Share-Alike 3.0 License
SparkFun: http://creativecommons.org/licenses/by-sa/3.0
SparkFun-Aesthetics: Licensing: CC v3.0 Share-Alike You are welcome to use this library for commercial purposes.
